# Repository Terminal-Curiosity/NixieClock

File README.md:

# Nixie Clock

A retro-style digital clock built with nixie tubes and an ESP32 microcontroller, custom built to fit into the scrap metal remains of an X-ray Tube.

## Features

- **Nixie Tube Display**: Classic nixie tube display showing time in HHMM format
- **2x Custom PCBs**: Designed to retrofit the X-ray Tube shell
- **RGB LED Backlight**: RGB LEDs behind each tube for added colour and dazzle
- **ESP32 Microcontroller**: Powered by an ESP32 Wroom32 microcontroller dev board
- **WiFi Time sync**: Daily time sync using wifi NTP to correct against clock drift and daylight savings
- **Cathode Protection**: daily nixie tube conditioning to prevent cathode poisoning

## Block Diagram

## Hardware

### Main Components

- **Microcontroller**: ESP32 Wroom32 DevKit-C
- **Nixie Tubes**: 4x IN-12 display
- **I/O Expansion**: 2x PCF8574 I2C I/O expanders
- **Decoders**: K155ID1 BCD-to-decimal decoders
- **Brightness Control**: Light Dependent Resistor (LDR)
- **Decoration LEDs**: 4x PL9823 RGB LEDs
- **High Voltage Supply**: NCH8200HV Nixie Power Booster Module

### Custom PCBs

The project includes Two custom PCB designs:

1. **NixieClock_ControlDaughterBoard**: Main control board with ESP32, HV Supply and LEDs
2. **NixieClock_NixieTubePanel**: Nixie tube display panel with decoder logic

### GPIO Pin Configuration

| Pin | Function |
|-----|----------|
| 4   | SDA1 (I2C Bus 1) |
| 15  | SCL1 (I2C Bus 1) |
| 21  | SDA2 (I2C Bus 2) |
| 22  | SCL2 (I2C Bus 2) |
| 19  | INT2 (Interrupt, unused) |
| 32  | RGB LED (NeoPixel) |
| 23  | HV Enable (High Voltage supply) |
| 33  | LDR (Analog input) |

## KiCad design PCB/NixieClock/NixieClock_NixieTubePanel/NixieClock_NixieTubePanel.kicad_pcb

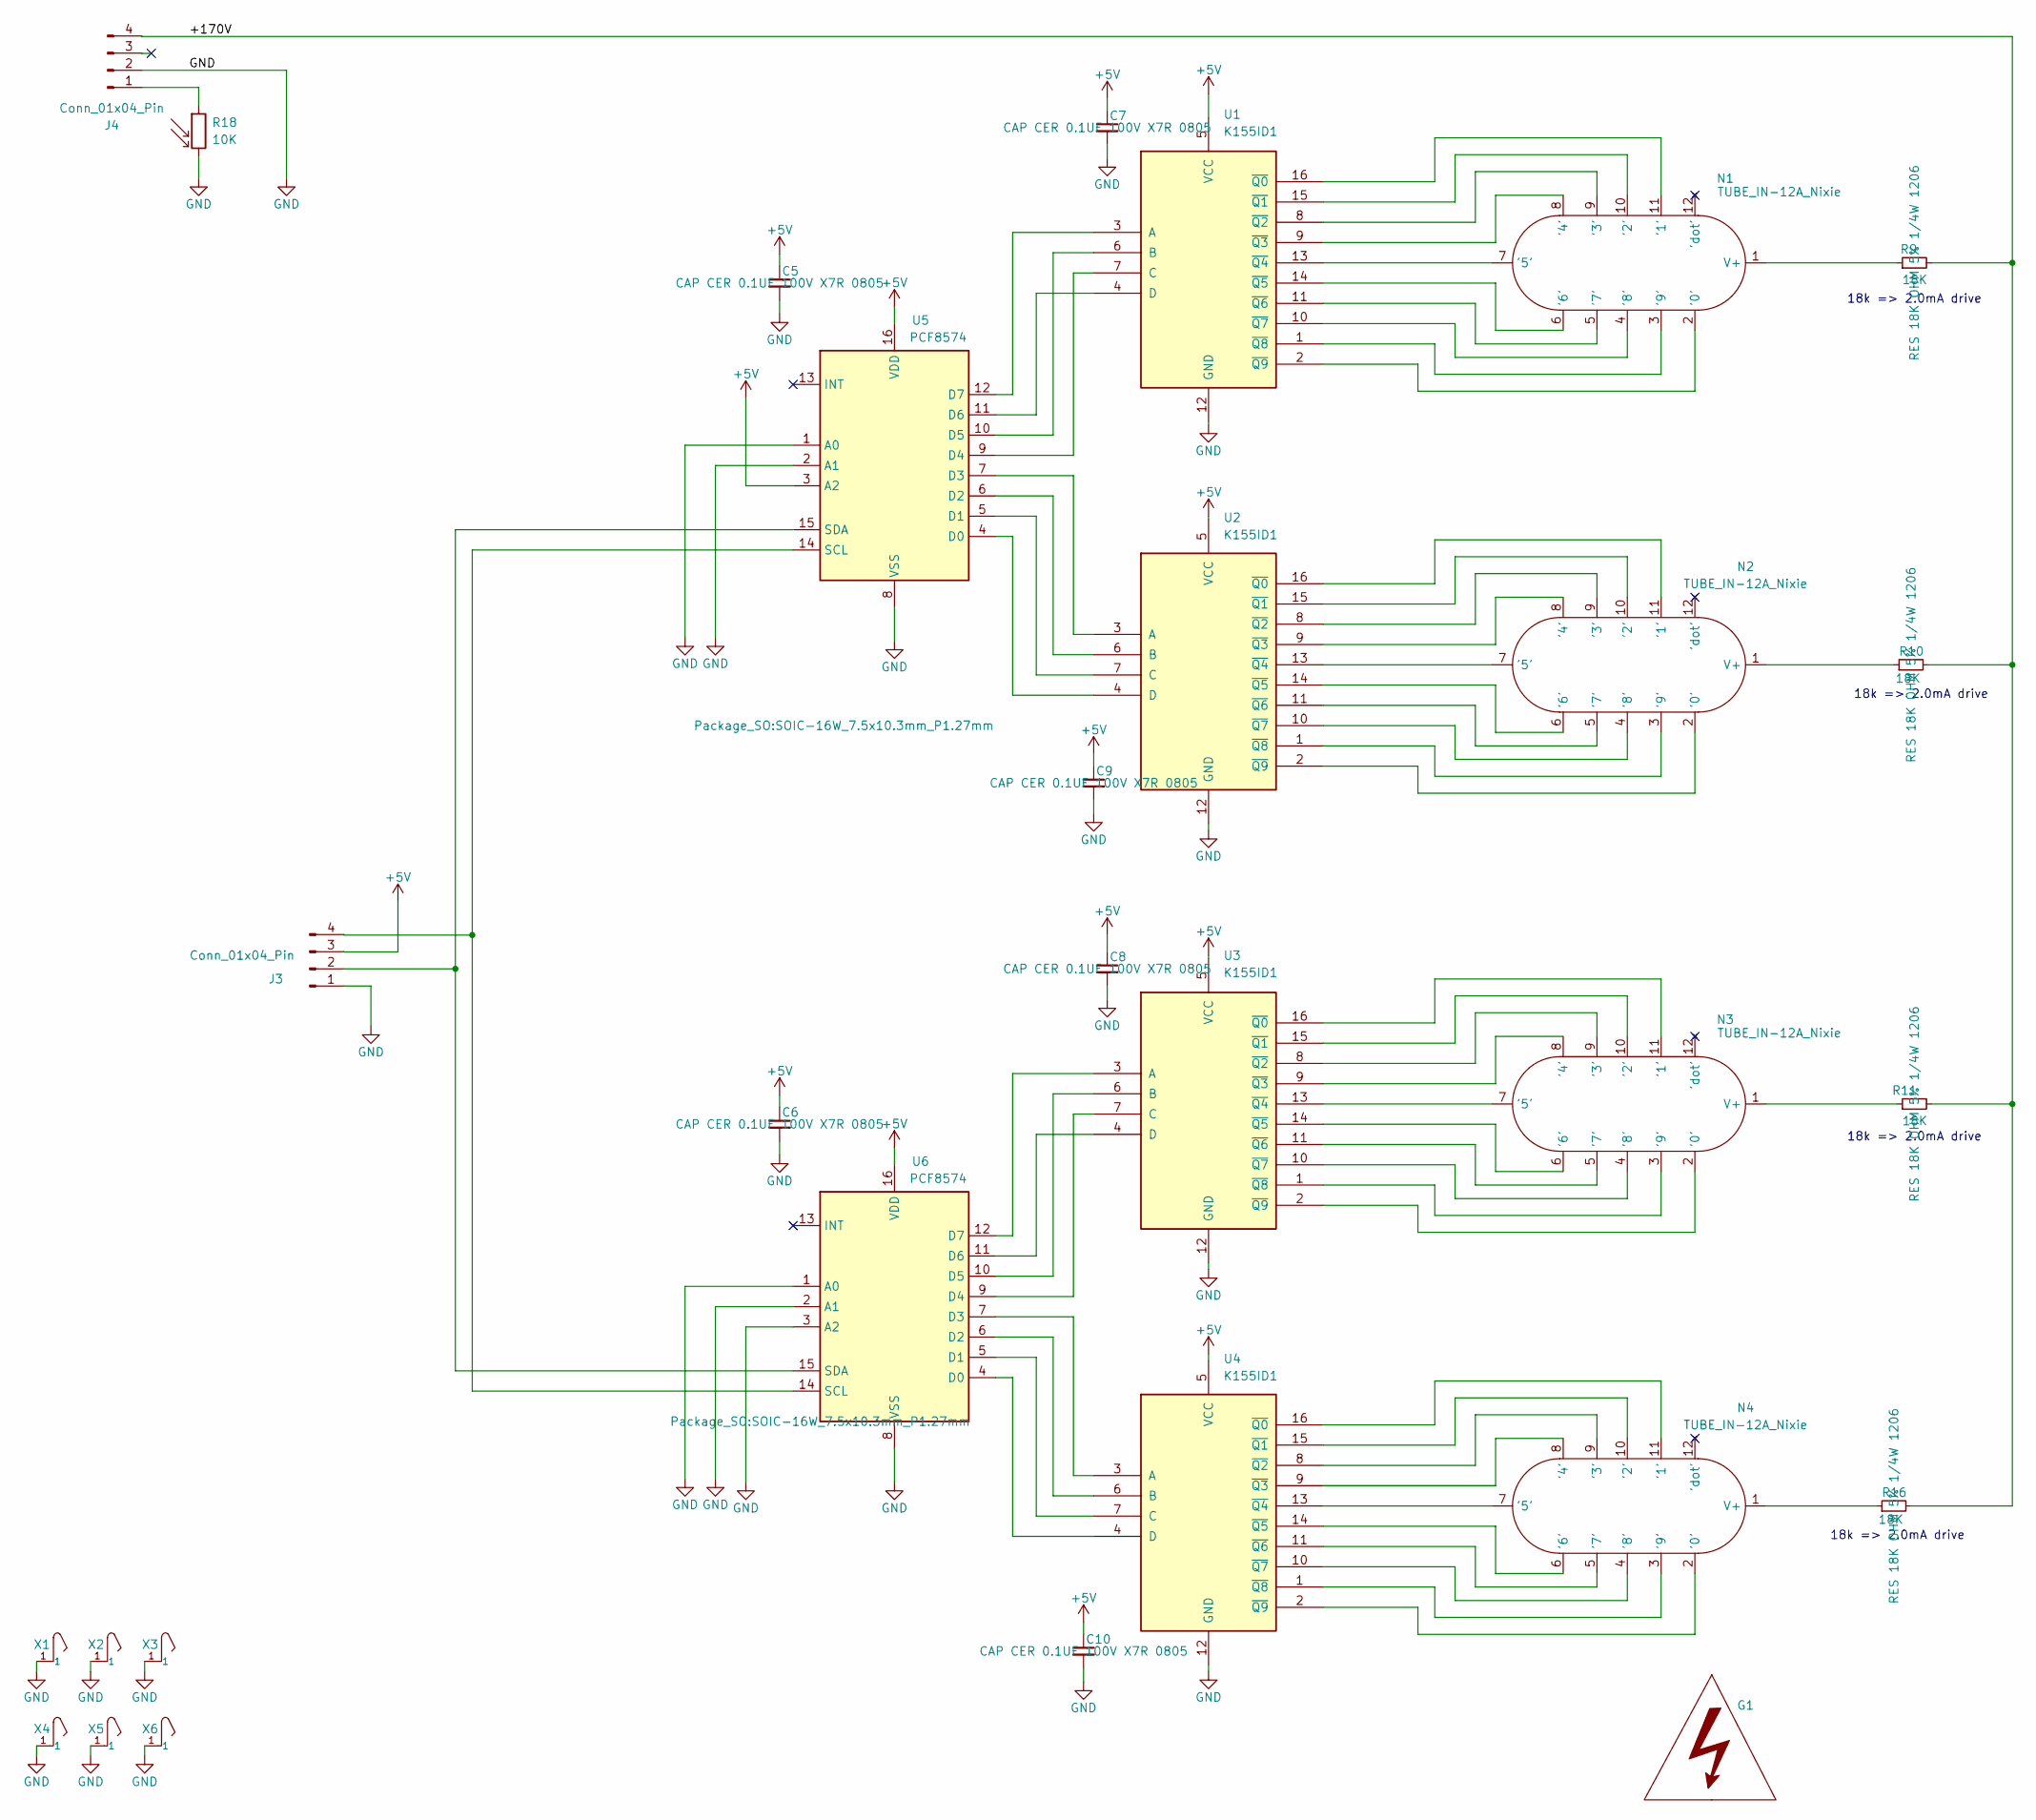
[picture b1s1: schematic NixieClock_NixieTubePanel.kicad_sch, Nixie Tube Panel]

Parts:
C5, C6, C7, C8, C9, C10: 100nF; C_0805_2012Metric_Pad1.18x1.45mm_HandSolder; Manufacturer PN CL21B104KCFNNNE
G1: LABEL_HVWarning
J3, J4: Conn_01x04_Pin; PinHeader_1x04_P2.54mm_Vertical; Manufacturer PN 61300411121
N1, N2, N3, N4: TUBE_IN-12A_Nixie; in-12_nixie-tube-socket; Manufacturer PN Unknown
R9, R10, R11, R16: 18K; R_1206_3216Metric_Pad1.30x1.75mm_HandSolder; Manufacturer PN RC1206JR-0718KL
R18: 10K; R_LDR_5.1x4.3mm_P3.4mm_Vertical; Manufacturer PN LDR07
U1, U2, U3, U4: K155ID1; DIP-16_W7.62mm; Manufacturer PN Unknown
U5, U6: PCF8574; SOIC-16W_7.5x10.3mm_P1.27mm; Manufacturer PN PCF8574ADWR
X1, X2, X3, X4, X5, X6: 5230; CONN-Batt-Spring-SMD-3.5mmX3.5mm; Manufacturer PN 122TR

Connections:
+5V: C5.1, C6.1, C7.1, C8.1, C9.1, C10.1, J3.3, U1.5 (VCC), U2.5 (VCC), U3.5 (VCC), U4.5 (VCC), U5.3 (A2), U5.16 (VDD), U6.16 (VDD)
/+170V: J4.4, R9.2, R10.2, R11.2, R16.2
GND: C5.2, C6.2, C7.2, C8.2, C9.2, C10.2, J3.1, J4.2, R18.2, U1.12 (GND), U2.12 (GND), U3.12 (GND), U4.12 (GND), U5.1 (A0), U5.2 (A1), U5.8 (VSS), U6.1 (A0), U6.2 (A1), U6.3 (A2), U6.8 (VSS), X1.1, X2.1, X3.1, X4.1, X5.1, X6.1
unnamed: J3.2, U5.15 (SDA), U6.15 (SDA)
unnamed: J3.4, U5.14 (SCL), U6.14 (SCL)
unnamed: J4.1, R18.1
unnamed: N1.2 ('0'), U1.2 (~Q9)
unnamed: N1.11 ('1'), U1.16 (~Q0)
unnamed: N1.10 ('2'), U1.15 (~Q1)
unnamed: N1.9 ('3'), U1.8 (~Q2)
unnamed: N1.8 ('4'), U1.9 (~Q3)
unnamed: N1.7 ('5'), U1.13 (~Q4)
unnamed: N1.6 ('6'), U1.14 (~Q5)
unnamed: N1.5 ('7'), U1.11 (~Q6)
unnamed: N1.4 ('8'), U1.10 (~Q7)
unnamed: N1.3 ('9'), U1.1 (~Q8)
unnamed: N1.1 (V+), R9.1
unnamed: N2.2 ('0'), U2.2 (~Q9)
unnamed: N2.11 ('1'), U2.16 (~Q0)
unnamed: N2.10 ('2'), U2.15 (~Q1)
unnamed: N2.9 ('3'), U2.8 (~Q2)
unnamed: N2.8 ('4'), U2.9 (~Q3)
unnamed: N2.7 ('5'), U2.13 (~Q4)
unnamed: N2.6 ('6'), U2.14 (~Q5)
unnamed: N2.5 ('7'), U2.11 (~Q6)
unnamed: N2.4 ('8'), U2.10 (~Q7)
unnamed: N2.3 ('9'), U2.1 (~Q8)
unnamed: N2.1 (V+), R10.1
unnamed: N3.2 ('0'), U3.2 (~Q9)
unnamed: N3.11 ('1'), U3.16 (~Q0)
unnamed: N3.10 ('2'), U3.15 (~Q1)
unnamed: N3.9 ('3'), U3.8 (~Q2)
unnamed: N3.8 ('4'), U3.9 (~Q3)
unnamed: N3.7 ('5'), U3.13 (~Q4)
unnamed: N3.6 ('6'), U3.14 (~Q5)
unnamed: N3.5 ('7'), U3.11 (~Q6)
unnamed: N3.4 ('8'), U3.10 (~Q7)
unnamed: N3.3 ('9'), U3.1 (~Q8)
unnamed: N3.1 (V+), R11.1
unnamed: N4.2 ('0'), U4.2 (~Q9)
unnamed: N4.11 ('1'), U4.16 (~Q0)
unnamed: N4.10 ('2'), U4.15 (~Q1)
unnamed: N4.9 ('3'), U4.8 (~Q2)
unnamed: N4.8 ('4'), U4.9 (~Q3)
unnamed: N4.7 ('5'), U4.13 (~Q4)
unnamed: N4.6 ('6'), U4.14 (~Q5)
unnamed: N4.5 ('7'), U4.11 (~Q6)
unnamed: N4.4 ('8'), U4.10 (~Q7)
unnamed: N4.3 ('9'), U4.1 (~Q8)
unnamed: N4.1 (V+), R16.1
unnamed: U1.3 (A), U5.12 (D7)
unnamed: U1.6 (B), U5.10 (D5)
unnamed: U1.7 (C), U5.9 (D4)
unnamed: U1.4 (D), U5.11 (D6)
unnamed: U2.3 (A), U5.7 (D3)
unnamed: U2.6 (B), U5.6 (D2)
unnamed: U2.7 (C), U5.5 (D1)
unnamed: U2.4 (D), U5.4 (D0)
unnamed: U3.3 (A), U6.12 (D7)
unnamed: U3.6 (B), U6.10 (D5)
unnamed: U3.7 (C), U6.9 (D4)
unnamed: U3.4 (D), U6.11 (D6)
unnamed: U4.3 (A), U6.7 (D3)
unnamed: U4.6 (B), U6.6 (D2)
unnamed: U4.7 (C), U6.5 (D1)
unnamed: U4.4 (D), U6.4 (D0)

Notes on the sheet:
18k => 2.0mA drive

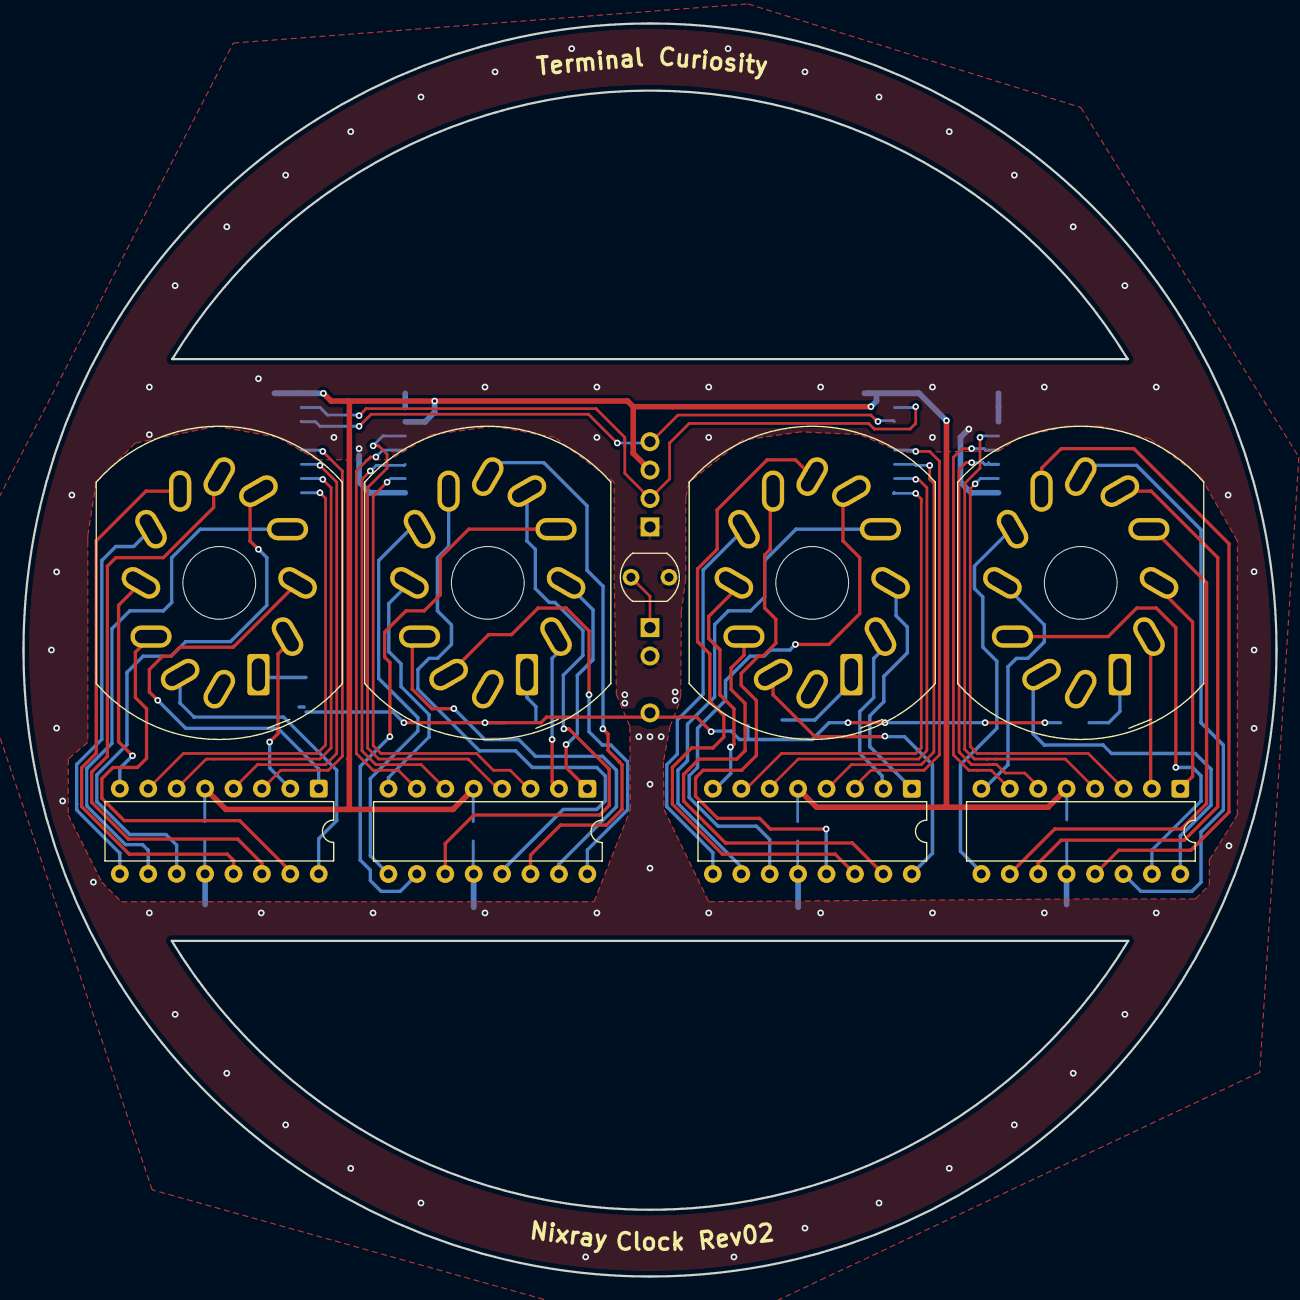
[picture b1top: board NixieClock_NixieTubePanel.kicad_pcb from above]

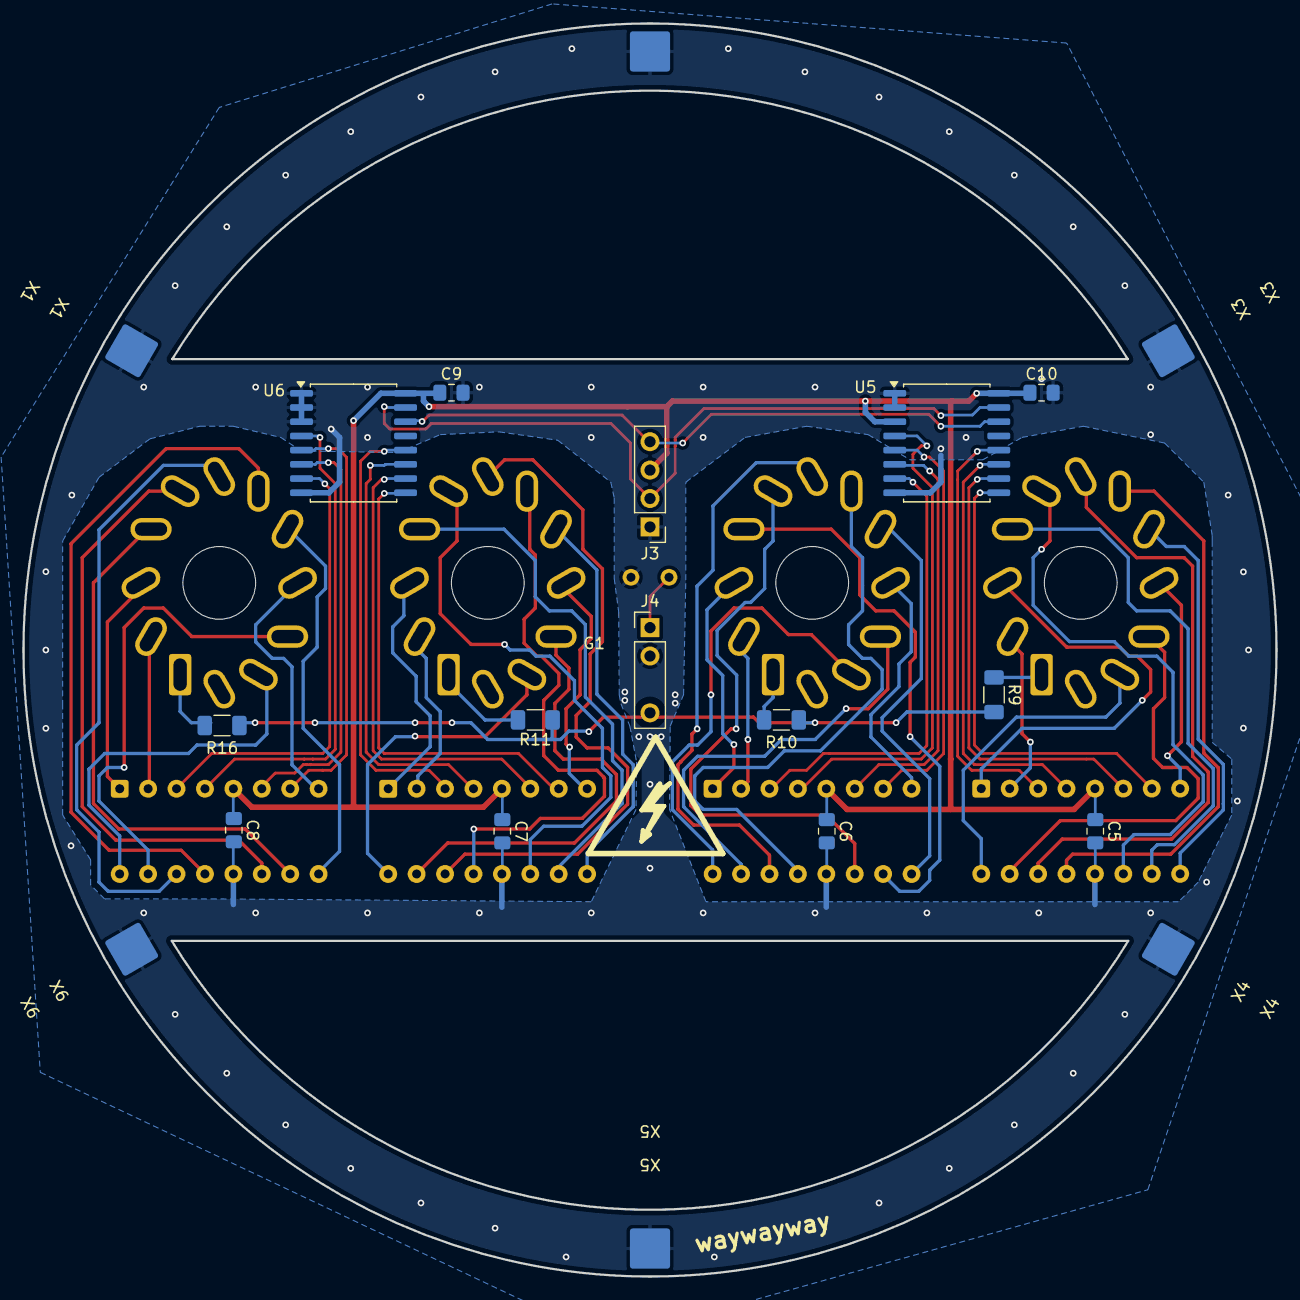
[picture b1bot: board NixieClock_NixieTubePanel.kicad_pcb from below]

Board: 2 copper layers, 112.0 x 112.0 mm, 30 parts (21 on the bottom side), 66 nets.

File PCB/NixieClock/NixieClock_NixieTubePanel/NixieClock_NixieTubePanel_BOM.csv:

"Reference","Value","Description","Qty","Manufacturer","Manufacturer PN","Supplier"
"X1,X2,X3,X4,X5,X6","5230","BATT CONTACT SOLID MULTIPLE SMD","6","Keystone Electronics","122TR","Digikey"
"U5,U6","PCF8574","PCF8574 8BIT I2C PORT EXPANDER","2","Texas Instruments","PCF8574ADWR","Digikey"
"U1,U2,U3,U4","K155ID1","K155ID1 NIXIE TUBE DRIVER IC","4","Unknown","Unknown","eBay"
"R18","10K","Light Dependent Resistor 10K 150V","1","LDR Photoresistors","LDR07","Unknown"
"R9,R10,R11,R16","18K","RES 18K OHM 5% 1/4W 1206","4","YAGEO","RC1206JR-0718KL","Digikey"
"N1,N2,N3,N4","TUBE_IN-12A_Nixie","IN-12A Nixie tube","4","Unknown","Unknown","eBay"
"J3,J4","Conn_01x04_Pin","Generic connector, single row, 01x04, script generated","2","Wurth Elektronik","61300411121","Digikey"
"C5,C6,C7,C8,C9,C10","100nF","CAP CER 0.1UF 100V X7R 0805","6","Samsung","CL21B104KCFNNNE","Digikey"

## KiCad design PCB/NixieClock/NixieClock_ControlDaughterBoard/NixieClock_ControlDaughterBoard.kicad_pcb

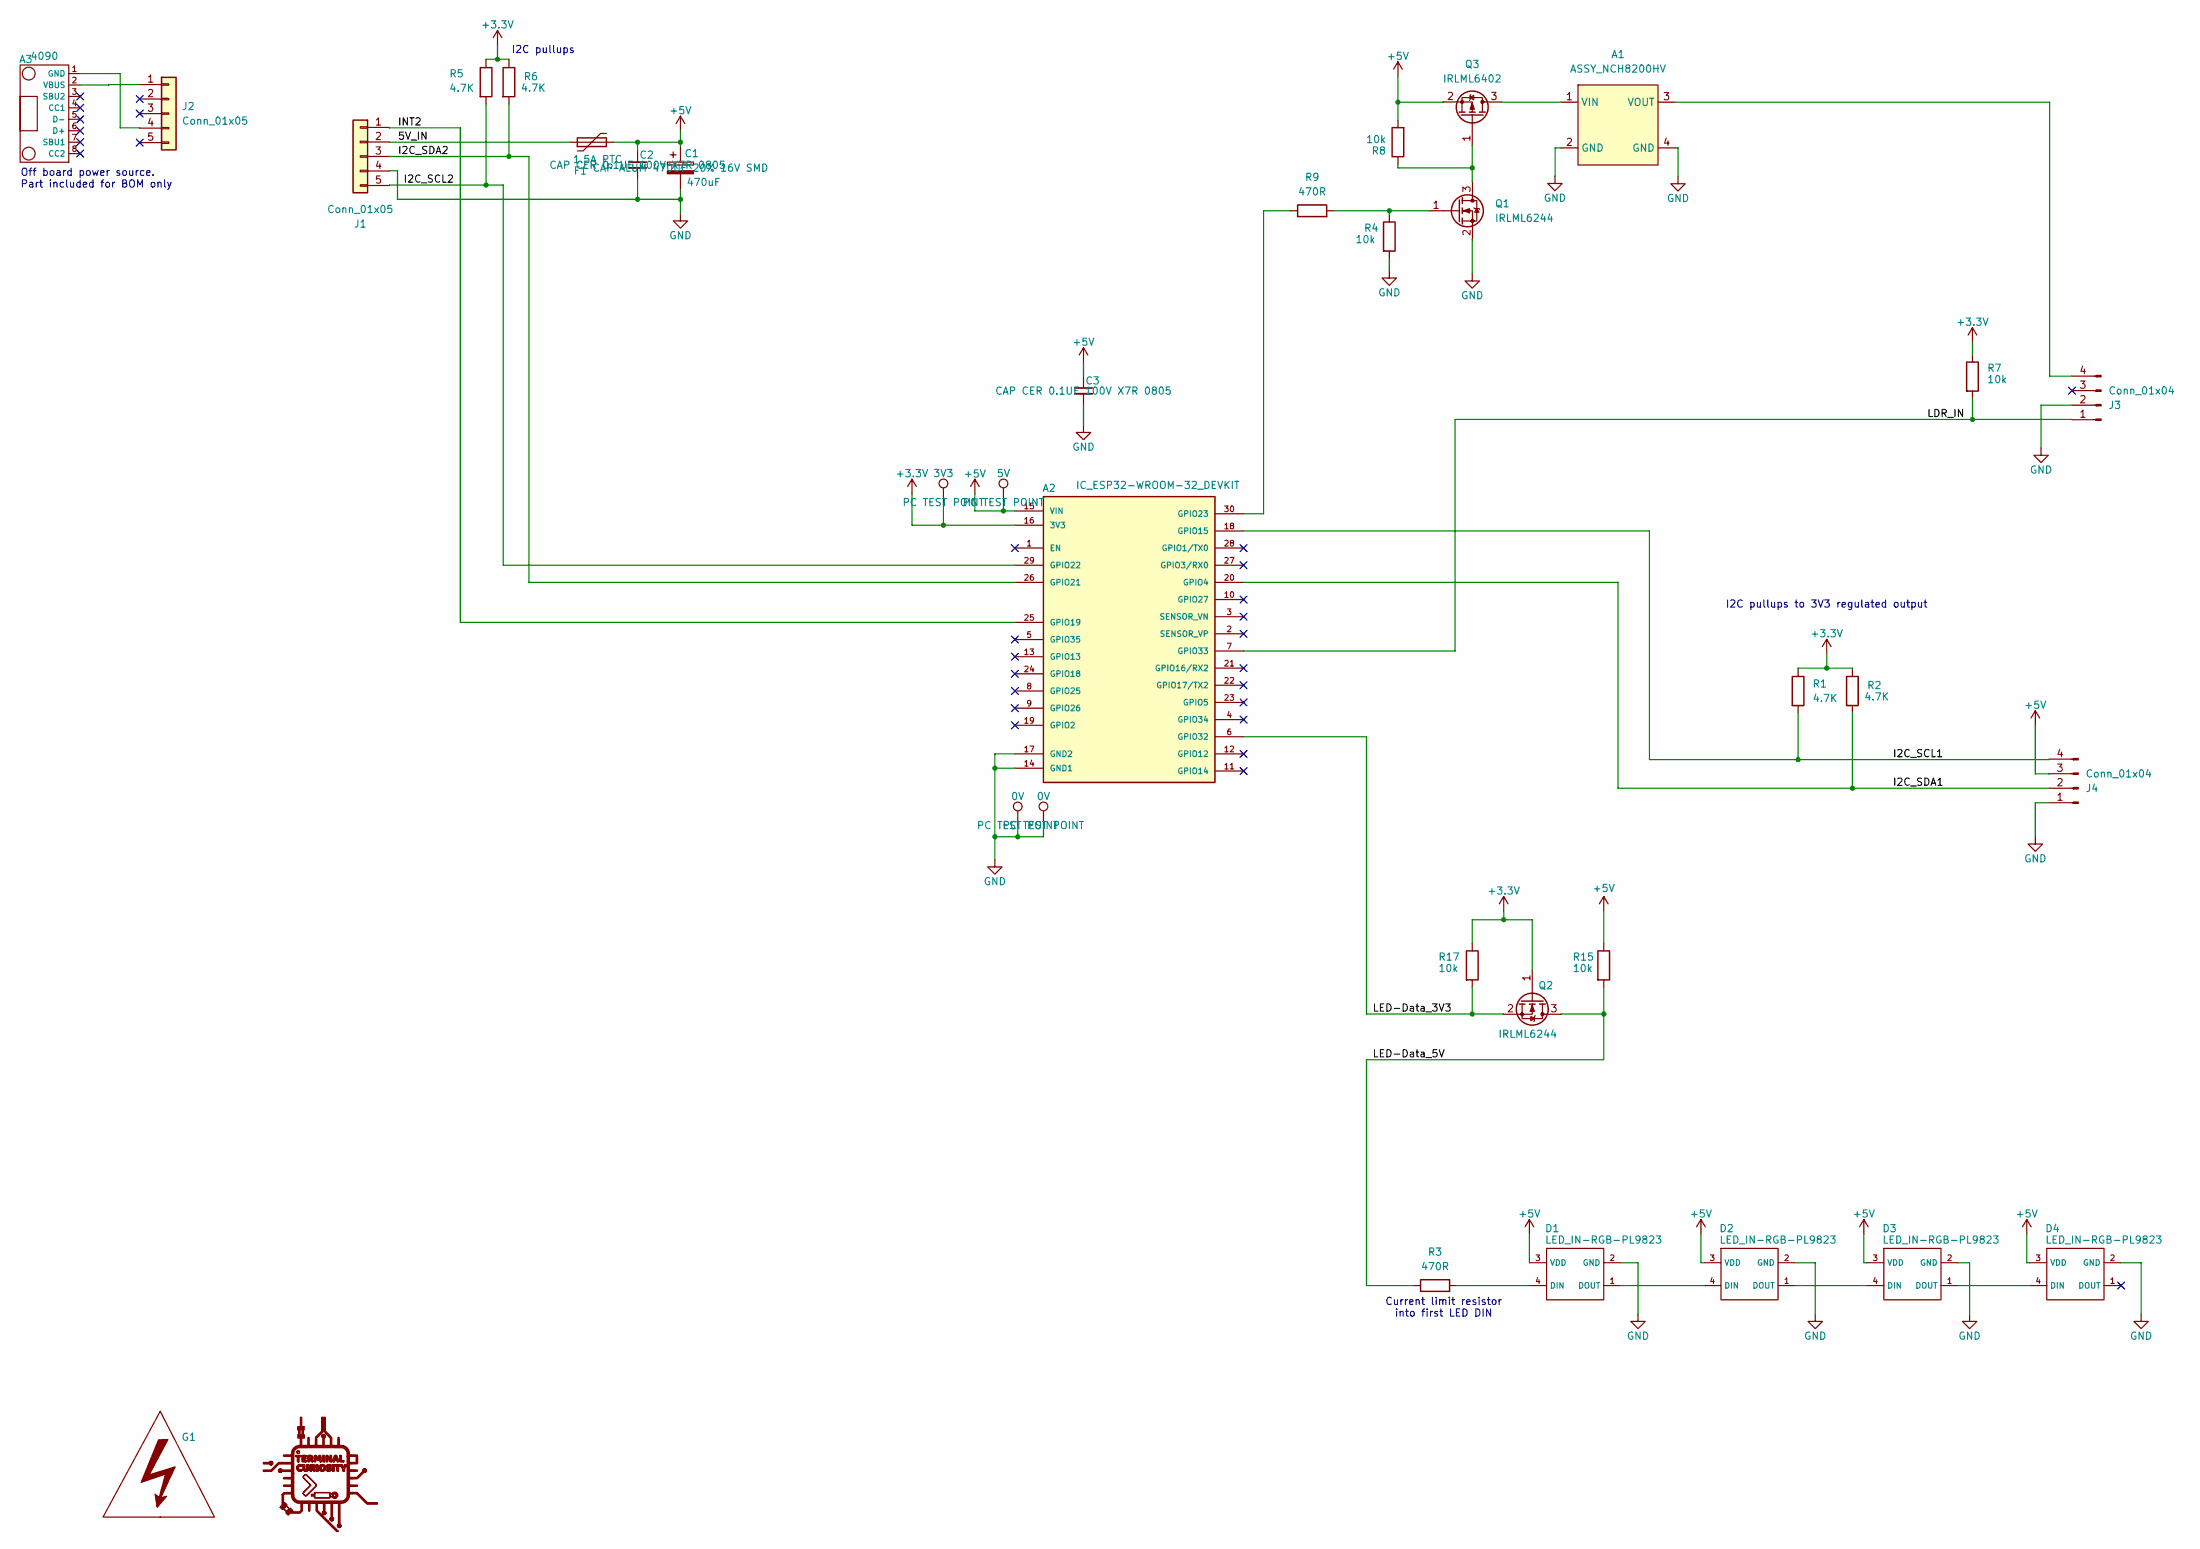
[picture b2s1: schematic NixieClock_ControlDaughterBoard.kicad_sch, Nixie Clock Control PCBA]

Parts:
A1: ASSY_NCH8200HV; NCH8200HV; Manufacturer PN ASSY_NCH8200HV
A2: IC_ESP32-WROOM-32_DEVKIT; MODULE_ESP32-DEVKITC-32D; Manufacturer PN ESP32-WROOM-32_DEVKIT
A3: 4090; Manufacturer PN 4090
C1: 470uF; CP_Elec_8x10; Manufacturer PN UWT1C471MNL1GS
C2, C3: 100nF; C_0805_2012Metric_Pad1.18x1.45mm_HandSolder; Manufacturer PN CL21B104KCFNNNE
D1, D2, D3, D4: LED_IN-RGB-PL9823; LED_D5.0mm-4_RGB; Manufacturer PN PL9823
F1: 1.5A PTC; R_1206_3216Metric_Pad1.30x1.75mm_HandSolder; Manufacturer PN NANOSMDC150F-2
G1: LABEL_HVWarning
G2: LOGO; LABEL_TerminalCuriosity_25.0x25.0mm
J1, J2: Conn_01x05; JST_XH_B5B-XH-A_1x05_P2.50mm_Vertical; Manufacturer PN B5B-XH-A
J3, J4: Conn_01x04; PinSocket_1x04_P2.54mm_Vertical; Manufacturer PN PPTC041LFBN-RC
Q1, Q2: IRLML6244; SOT-23; Manufacturer PN IRLML6244TRPBF
Q3: IRLML6402; SOT-23; Manufacturer PN IRLML6402TRPBF
R1, R2, R5, R6: 4.7K; R_0805_2012Metric_Pad1.20x1.40mm_HandSolder; Manufacturer PN RC0805JR-074K7L
R3, R9: 470R; R_0805_2012Metric_Pad1.20x1.40mm_HandSolder; Manufacturer PN RC0805FR-07470RL
R4, R7, R8, R15, R17: 10k; R_0805_2012Metric_Pad1.20x1.40mm_HandSolder; Manufacturer PN RC0805FR-1310KL
TP1: 5V; TestPoint_Pad_2.0x2.0mm; Manufacturer PN RCUCTE
TP2: 3V3; TestPoint_Pad_2.0x2.0mm; Manufacturer PN RCUCTE
TP5, TP6: 0V; TestPoint_Pad_2.0x2.0mm; Manufacturer PN RCUCTE

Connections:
+3.3V: A2.16 (3V3), Q2.1 (G), R1.1, R2.1, R5.1, R6.1, R7.1, R17.1, TP2.1
+5V: A2.15 (VIN), C1.1, C2.1, C3.1, D1.3 (VDD), D2.3 (VDD), D3.3 (VDD), D4.3 (VDD), F1.2, J4.3, Q3.2 (S), R8.2, R15.1, TP1.1
/5V_IN: F1.1, J1.2
/I2C_SCL1: A2.18 (GPIO15), J4.4, R1.2
/I2C_SCL2: A2.29 (GPIO22), J1.5, R5.2
/I2C_SDA1: A2.20 (GPIO4), J4.2, R2.2
/I2C_SDA2: A2.26 (GPIO21), J1.3, R6.2
/INT2: A2.25 (GPIO19), J1.1
/LDR_IN: A2.7 (GPIO33), J3.1, R7.2
/LED-Data_3V3: A2.6 (GPIO32), Q2.2 (S), R17.2
/LED-Data_5V: Q2.3 (D), R3.1, R15.2
GND: A1.2 (GND), A1.4 (GND), A2.14 (GND1), A2.17 (GND2), C1.2, C2.2, C3.2, D1.2 (GND), D2.2 (GND), D3.2 (GND), D4.2 (GND), J1.4, J3.2, J4.1, Q1.2 (S), R4.2, TP5.1, TP6.1
unnamed: A1.1 (VIN), Q3.3 (D)
unnamed: A1.3 (VOUT), J3.4
unnamed: A2.30 (GPIO23), R9.1
unnamed: A3.1 (GND), J2.4
unnamed: A3.2 (VBUS), J2.1
unnamed: D1.4 (DIN), R3.2
unnamed: D1.1 (DOUT), D2.4 (DIN)
unnamed: D2.1 (DOUT), D3.4 (DIN)
unnamed: D3.1 (DOUT), D4.4 (DIN)
unnamed: Q1.3 (D), Q3.1 (G), R8.1
unnamed: Q1.1 (G), R4.1, R9.2

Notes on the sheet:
I2C pullups
Current limit resistor into first LED DIN
I2C pullups to 3V3 regulated output
Off board power source. Part included for BOM only

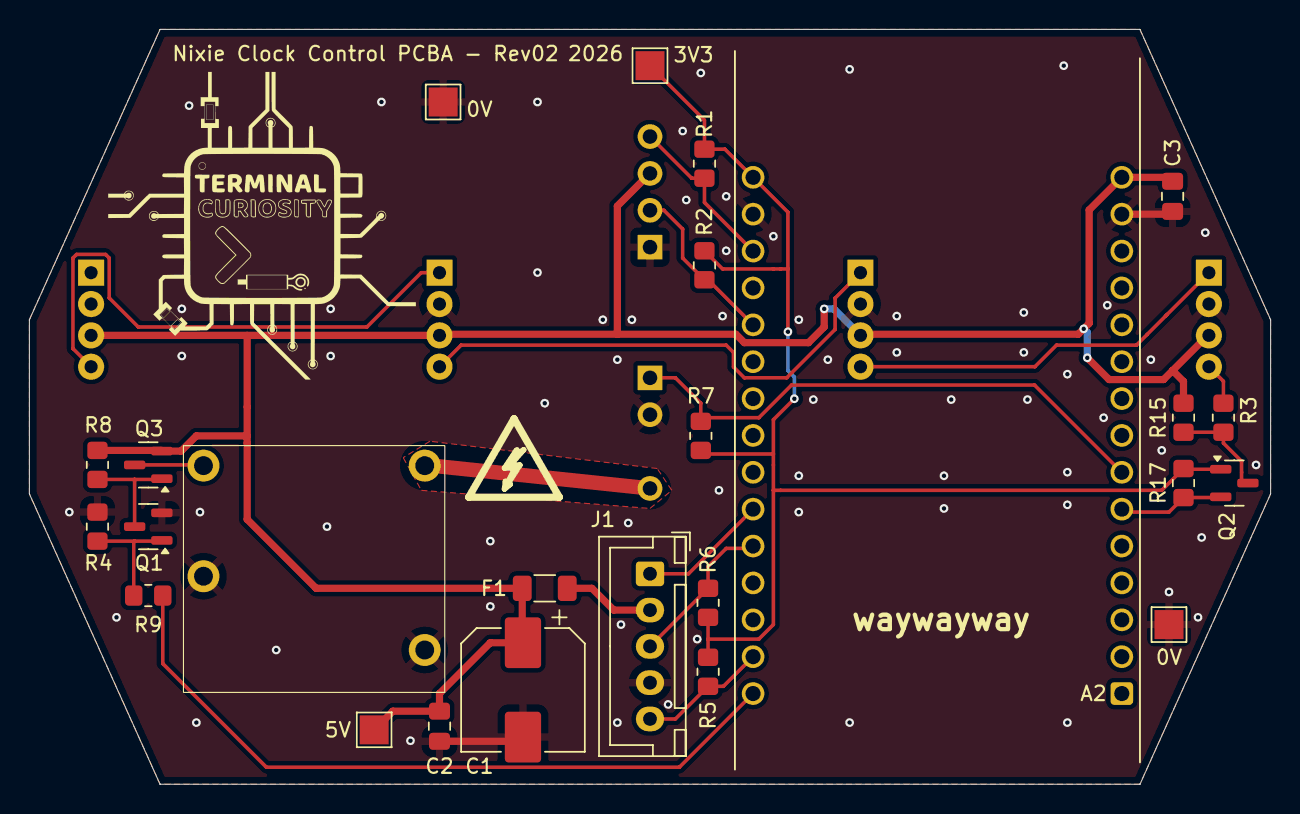
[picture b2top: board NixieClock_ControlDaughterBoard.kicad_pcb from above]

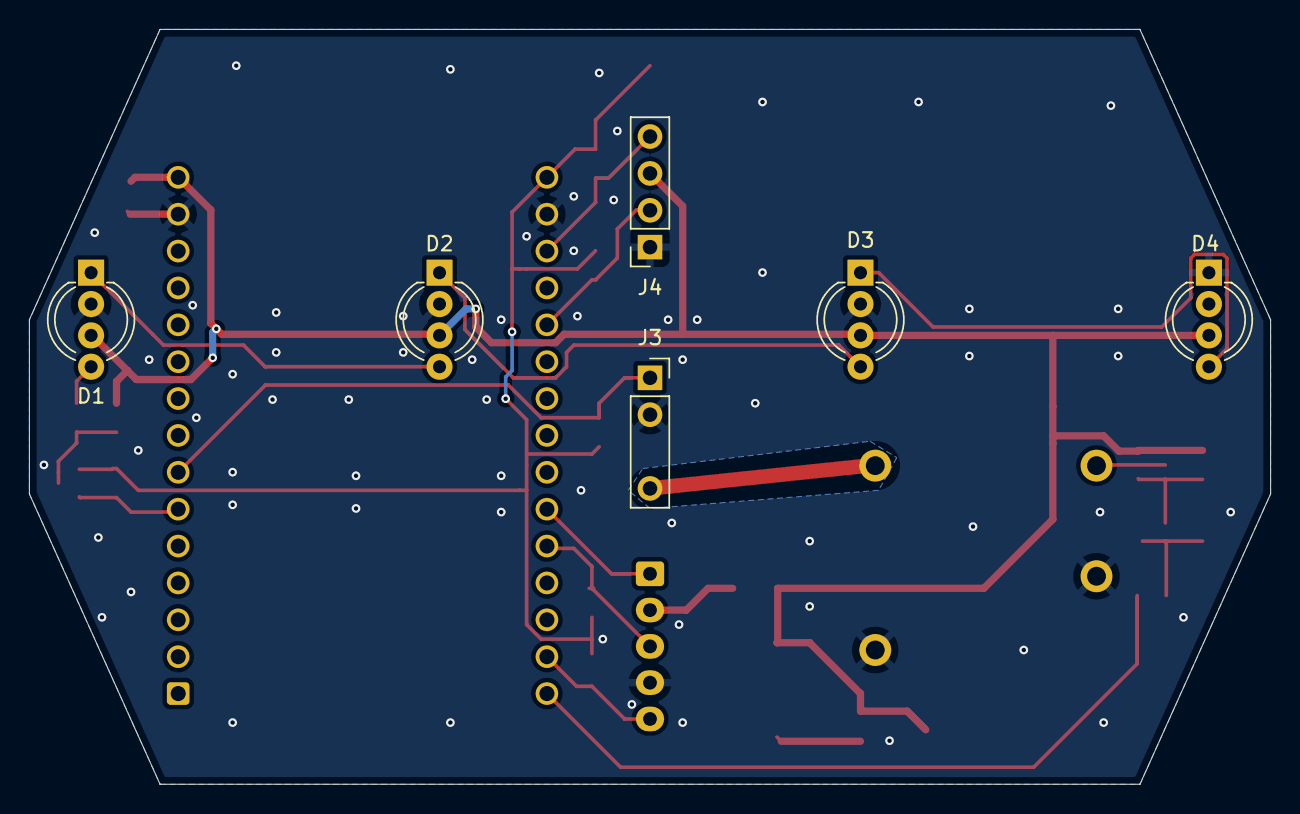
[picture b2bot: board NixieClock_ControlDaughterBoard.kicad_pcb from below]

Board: 2 copper layers, 85.5 x 52.0 mm, 33 parts (6 on the bottom side), 21 nets.

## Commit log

2023-06-19 Commit Nixie Clock files
2025-06-11 nixie panel PCB layout progress
    laid out tube 1 with top and bottom traces. added GND polygon on both sides, with exception zone around tube 1. tubes 2-4 to be laid out with top and bottom traces
2025-06-11 separated Nixie clock firmware to different repo
    added nixie clock firmware to git ignore so that it is removed from this repo and can be captured in its own separate repo
2025-06-11 Nixie driver board - single board
    Capture state of files for nixie driver board before splitting into two separate boards.
    delete temporary files that open only when kicad is open and are not needed in git.
2025-06-13 complete tube 2 wiring
    complete trace layout for tube 2 on top and bot side
2025-06-13 tidied .gitignore file
    removed many individual "ignore this file" references and replaced with fewer "ignore filetype" references
2025-06-13 fix typo in previous .gitignore commit
    fp-info-cache was not being ignored as expected. fixed this
2025-06-13 tube 2 checkpoint
    tubes 1 and 2 have been routed using top/bot traces. saving checkpoint before rerouting tube 3 the same
2025-06-13 Tube 3 wiring complete
    Tube 3 wiring top/bot complete. tube 4 started
2025-06-13 Tidied U1 and U3 connections
    adjust pin ordering on U1 and U3 in schematic so they would connect to the PCF chips neater on the PCB without needing vias
2025-06-13 change driver 3 ground trace to back side
    rerouted some traces so that driver chip 3 ground trace can run on the back instead of the front, which looks neater and matches the other 3 chips
2025-06-19 Route tube 4
    Finished routing tube 4 top and bottom traces
2025-06-19 add Polygon pour + stitching vias
    Add polygon ground pour to top and bottom. add stitching vias all around board for improved layer connection. add polygon keepout zones to keep ground plane away from HV components
2025-06-30 mid-DRC review
    mid review checkpoint. errors require reloading footprints from library, which might break a lot of things. This checkpoint captures last good state
2025-06-30 DRC cleared
    0 DRC errors
2025-06-30 Tidied messy polygon generation around R18
    Polygon bridge from top to bottom was narrowed but then it created plane discontinuities so this widened it again slightly. DRC zero
2025-06-30 Tidied +170V trace slightly
    some unnecessary diagonal lines were removed
2025-06-30 increase HV clearance on U3:8 trace
    moved trace further from LV signals
2025-06-30 Remove windows explorer shortcut
    Not needed in project repo
2025-06-30 Move Monoboard files to Archive
    Monoboard files to be split into two separate PCBs because the monoboard PCB shape is too small. files moved to archive for reference but not for development
2025-06-30 Removed dead files
    remove dead files
2025-06-30 ignore .zip files instead
    simplify gitignore to ignore .zip files instead of specific backup folders that might get moved around
2025-07-14 Fix SMD components missing B.Paste
    change B.Paste clearance to 0 to return paste on SMD components.
    Paste not necessary because hand soldering, but its good practice
2025-07-20 Layout WIP
    lock in locations of mech-critical components (LEDs, connectors) and initial layout of non mech-critical components.
    next step: define trace rules and start wiring layout
2025-07-20 Remove unconnected pin3 on J4
    pin3 was not electrically connected. removing it creates better creepage between HV pin 4 and LV pin 2
2025-07-20 Layout WIP
    layout half completed.
    +5V net class added to SCH so it has thicker traces on PCB
2025-07-21 Add current limit resistor to N-MOS base
    needed to limit current into N-MOS during switching on. improves EMI and protects gate/esp driver from excessive current.
2025-07-21 layout draft1 complete
    completed all pcb routing and polygon pour.
    Changed LED footprints to wide pins. previously they had 0.085mm clearance between pads, which is too tight to manufacture. wide pins have 0.36mm min (14mil) which is above PCBway suggested 6mil.
    Removed all DRC errors.
    Some warnings exist for ESP32 silkscreen beyond board border, but this is ok for the assembly overall
2025-07-21 remove text note to self
    text note no longer needed
2025-07-21 add pdfs to gitignore
    schematic and assembly drawing outputs dont need to be added to git as they can be generated from controlled files
2025-07-22 Increase height by 2mm
    increase short side height from 50mm to 52mm to match the exact length of the ESP32 devkit PCBA.
    without this, the ESP would extend past this panel PCB by 1mm on both sides and would be visible from behind the clock
2025-07-22 Add dimensions to square section
    add dimensions for readability
2025-07-22 PCB layout 2 complete
    layout 1 was incorrect as the connectors and LEDs were not located in the right place to correctly mate with the tube panel PCBA. When connectors and LEDs were moved, all the traces became scrambled.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
    ESP32 pins were also remapped to improve ease of wiring
2025-07-29 Firmware Stably counting 0-9 at 1Hz
    firmware compiles and counts 0-9 at 1Hz. GPIOs have been configured as per PCB to verify function
2025-07-29 Move Rev1 firmware to archive
    not used anymore for development. just for reference
2025-07-29 I2C pin remap based on breadboard tests
    tested I2C pin mappings on breadboard and found that using GPIO2 caused the board to get stuck in boot mode. remapped to adjacent pin GPIO4 for safety.
2025-07-29 breadboard Firmware Rev2 WIP
    - compiles
    - counts 0-9 on single nixie tube at 1Hz
    - nixie tube brightness is controlled by LDR which sets duty cycle
    - brightness duty and 1sec tick are controlled by hardware timers
    - 4x RGB LEDs cycle through 10 colours in sync with 1sec tick
2025-08-29 Increase clearance to LED holes in tube centres
    moved traces to provide more creepage/clearance to 6mm holes in the centre of the nixie tube sockets and prevent HV issues to LEDs that will be positioned there
2025-08-29 Increased solder mask clearance to 0.3mm around tube socket centre holes
    to increase HV clearance area and safety at the component level wrt centre hole (and any LEDs inside said hole)
2025-08-30 tidy labels and adjacent vias
    aligned silkscreen labels and moved nearby vias to not conflict
2025-08-30 Tidy component details and add BOM
    fill missing supplier/mfr info on resistors and caps. export BOM
2025-08-30 Fill component details and export BOM
    filled missing component information, exported BOM
2025-08-30 Rename bom file to [project]_BOM
    Rename bom file to [project]_BOM as generated by SCH file
2025-09-01 disabled tube PWM brightness control timers
    theoretical research suggests that PWM control and smaller driving current in the tubes will cause increased wear and degradation. Running the tubes at 2mA even in a dark room is not too bright. seem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
2025-09-01 Change anode resistors from 0805 to 1206 for increased power headroom
    changed resistors and adjusted traces to suit.
    0805 resistors have Pmax 0.125W. if the PSU drifts up to 180-185V, it may exceed this power rating.
    1206 doubles the headroom
2025-09-01 Correct part details from 0805 to 1206 missed in previous commit
    also correct BOM
2025-09-01 Add 2025 to silkscreen
    add current year to project silkscreen. regenerate gerbers to suit
2026-01-01 decoupling caps 0603 -> 0805 for easier soldering
    prototype feedback found that decoupling caps can be 0805 sized and easier to hand solder. 0603 is not required
2026-01-01 swap pins 1,2 on LEDs
    LED pin layout was mistakenly swapped. discovered on Rev01 prototype. swapped pins in the SCH and PCB files. updated assembly to Rev02
2026-01-03 fixed power in pin (1->2)
    J2 5V pin was mistakenly wired to pin 1 instead of pin 2 (like on the control board connector J1)
2026-01-08 Rev03 files initial commit
    Rev03 represents the 3rd attempt at rewriting the code and also marks the transition from Arduino IDE to VScode (and hence C to C++).
2026-01-08 Rev02 final WIP
    add LDR sensor code, add basic colour cycling to test LEDs. after this commit, rev03 becomes the primary development
2026-01-08 Archive Rev2 files
2026-01-08 Restructure the project directories and files
2026-01-08 ignore PIO files
    not needed in repo
2026-01-08 WIP
    playing with file structures
2026-01-08 Restore datasheets and docs
    restoring files that were mistakenly removed
2026-01-31 consolidate project datasheets and images
2026-01-31 Move firmware files to a separate project
    refer to NixieClockFirmware project
2026-01-31 tidy project structure
2026-01-31 One LED did not update to the correct footprint
    the pins were still reversed from the original error. fixed that and regenerated polygon pour
2026-01-31 changed folder name "_PCB" -> "PCB" and deleted duplicate PCB files.
    project structure contained _PCB folder and PCB folder, both containing duplicate kicad files. PCB folder appeared to be junk and outdated files so was deleted and _PCB folder was renamed to PCB
2026-02-12 Update Readme
    improved clarity. removed unnecessary information
2026-02-12 remove duplicate image display
2026-02-12 component manufacturer details were incorrect
    deleted "MANUFACTURER" and "MANUFACTURER P/N" fields. now using "Manufacturer" "Manufacturer PN" consistently across project
2026-02-12 ignore autosave files
2026-02-12 vscode files not needed as firmware was moved to a separate repo
